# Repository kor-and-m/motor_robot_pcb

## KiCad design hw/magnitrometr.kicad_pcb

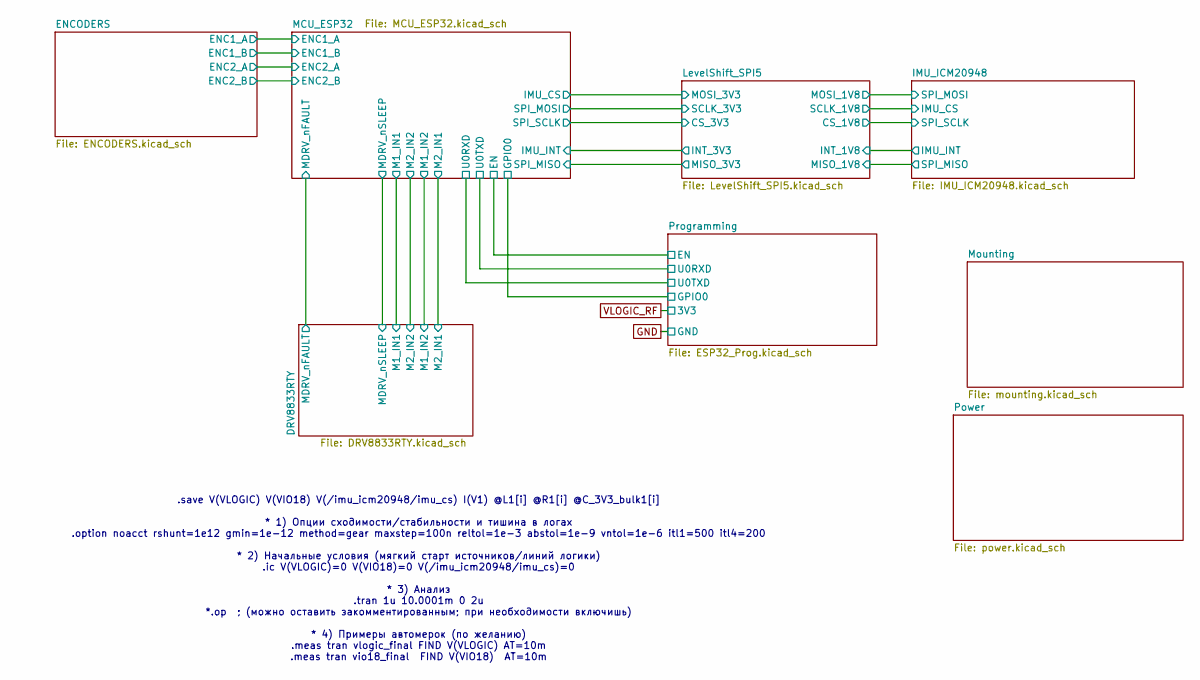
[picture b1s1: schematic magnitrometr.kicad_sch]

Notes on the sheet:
.save V(VLOGIC) V(VIO18) V(/imu_icm20948/imu_cs) I(V1) @L1[i] @R1[i] @C_3V3_bulk1[i] * 1) Опции сходимости/стабильности и тишина в логах .option noacct rshunt=1e12 gmin=1e-12 method=gear maxstep=100n reltol=1e-3 abstol=1e-9 vntol=1e-6 itl1=500 itl4=200 * 2) Начальные условия (мягкий старт источнико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

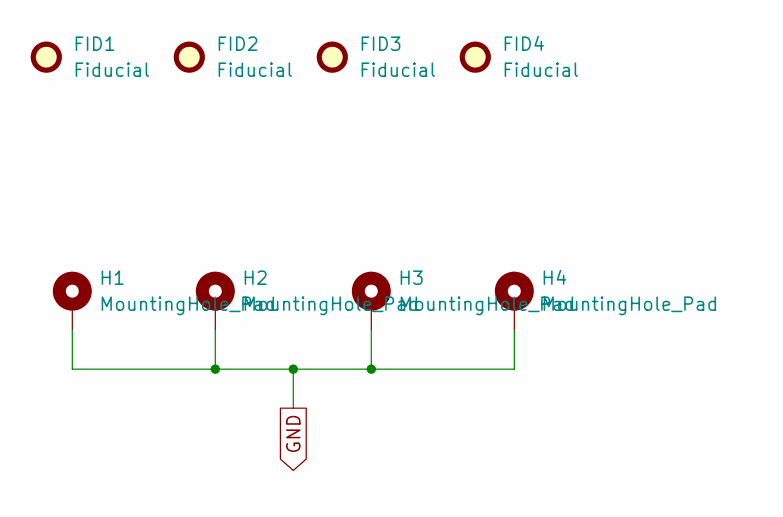
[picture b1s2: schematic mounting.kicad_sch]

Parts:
FID1, FID2, FID3, FID4: Fiducial; Fiducial_1.5mm_Mask3mm
H1, H2, H3, H4: MountingHole_Pad; MountingHole_3.2mm_M3_Pad

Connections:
GND: H1.1, H2.1, H3.1, H4.1; also elsewhere on the board

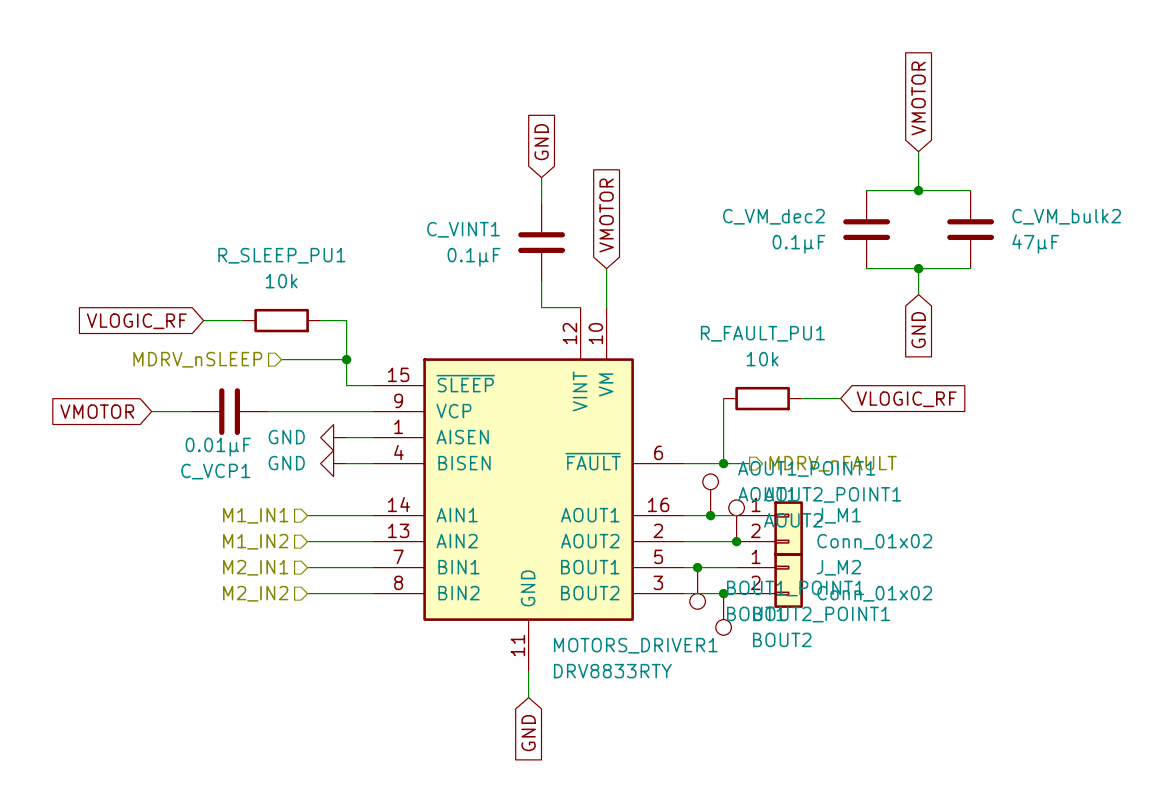
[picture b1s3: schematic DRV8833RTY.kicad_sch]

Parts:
AOUT1_POINT1: AOUT1; TestPoint_Pad_1.0x1.0mm
AOUT2_POINT1: AOUT2; TestPoint_Pad_1.0x1.0mm
BOUT1_POINT1: BOUT1; TestPoint_Pad_1.0x1.0mm
BOUT2_POINT1: BOUT2; TestPoint_Pad_1.0x1.0mm
C_VCP1: 0.01µF; C_0603_1608Metric
C_VINT1: 0.1µF; C_0603_1608Metric
C_VM_bulk2: 47µF; CP_Elec_5x5.8
C_VM_dec2: 0.1µF; C_0603_1608Metric
J_M1, J_M2: Conn_01x02; JST_VH_B2P-VH-B_1x02_P3.96mm_Vertical
MOTORS_DRIVER1: DRV8833RTY; Texas_RTY_WQFN-16-1EP_4x4mm_P0.65mm_EP2.1x2.1mm_ThermalVias
R_FAULT_PU1: 10k; R_0612_1632Metric
R_SLEEP_PU1: 10k; R_0612_1632Metric

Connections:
/DRV8833RTY/M1_IN1: MOTORS_DRIVER1.14 (AIN1); also elsewhere on the board
/DRV8833RTY/M1_IN2: MOTORS_DRIVER1.13 (AIN2); also elsewhere on the board
/DRV8833RTY/M2_IN1: MOTORS_DRIVER1.7 (BIN1); also elsewhere on the board
/DRV8833RTY/M2_IN2: MOTORS_DRIVER1.8 (BIN2); also elsewhere on the board
/DRV8833RTY/MDRV_nFAULT: MOTORS_DRIVER1.6 (~FAULT), R_FAULT_PU1.1; also elsewhere on the board
/DRV8833RTY/MDRV_nSLEEP: MOTORS_DRIVER1.15 (~SLEEP), R_SLEEP_PU1.2; also elsewhere on the board
GND: C_VINT1.1, C_VM_bulk2.2, C_VM_dec2.2, MOTORS_DRIVER1.1 (AISEN), MOTORS_DRIVER1.4 (BISEN), MOTORS_DRIVER1.11 (GND), MOTORS_DRIVER1.17 (GND); also elsewhere on the board
unnamed: AOUT1_POINT1.1, J_M1.1, MOTORS_DRIVER1.16 (AOUT1)
unnamed: AOUT2_POINT1.1, J_M1.2, MOTORS_DRIVER1.2 (AOUT2)
unnamed: BOUT1_POINT1.1, J_M2.1, MOTORS_DRIVER1.5 (BOUT1)
unnamed: BOUT2_POINT1.1, J_M2.2, MOTORS_DRIVER1.3 (BOUT2)
unnamed: C_VCP1.1, MOTORS_DRIVER1.9 (VCP)
unnamed: C_VINT1.2, MOTORS_DRIVER1.12 (VINT)
VLOGIC_RF: R_FAULT_PU1.2, R_SLEEP_PU1.1; also elsewhere on the board
VMOTOR: C_VCP1.2, C_VM_bulk2.1, C_VM_dec2.1, MOTORS_DRIVER1.10 (VM); also elsewhere on the board

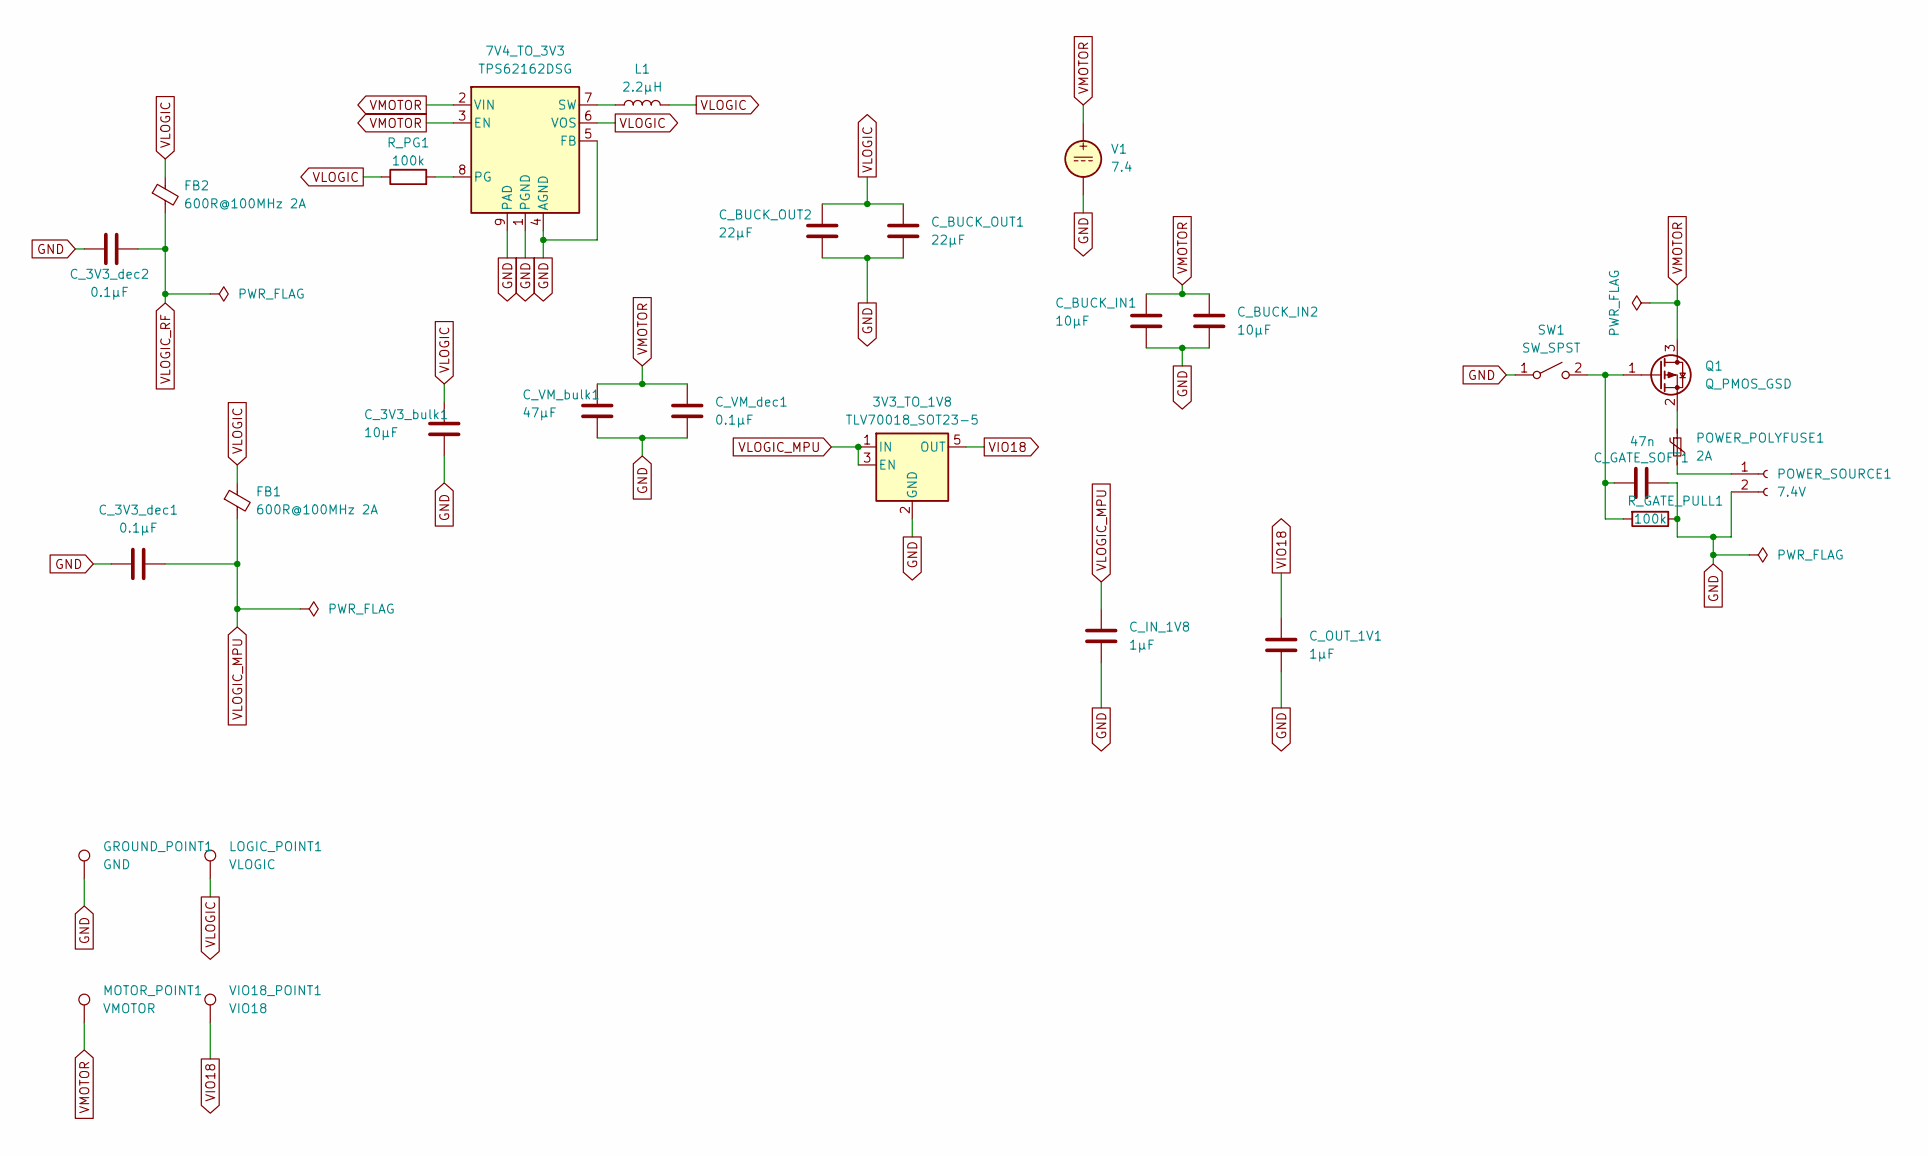
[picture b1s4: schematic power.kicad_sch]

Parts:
3V3_TO_1V8: TLV70018_SOT23-5; SOT-23-5
7V4_TO_3V3: TPS62162DSG; WSON-8-1EP_2x2mm_P0.5mm_EP0.9x1.6mm_ThermalVias
C_3V3_bulk1: 10µF; C_0805_2012Metric
C_3V3_dec1, C_3V3_dec2: 0.1µF; C_0603_1608Metric
C_BUCK_IN1, C_BUCK_IN2: 10µF; C_0805_2012Metric
C_BUCK_OUT1, C_BUCK_OUT2: 22µF; C_0805_2012Metric
C_GATE_SOFT1: 47n; C_0805_2012Metric
C_IN_1V8: 1µF; C_0603_1608Metric
C_OUT_1V1: 1µF; C_0603_1608Metric
C_VM_bulk1: 47µF; CP_Elec_5x5.8
C_VM_dec1: 0.1µF; C_0603_1608Metric
FB1, FB2: 600R@100MHz 2A; L_0805_2012Metric
GROUND_POINT1: GND; TestPoint_Pad_1.0x1.0mm
L1: 2.2µH; L_1008_2520Metric
LOGIC_POINT1: VLOGIC; TestPoint_Pad_1.0x1.0mm
MOTOR_POINT1: VMOTOR; TestPoint_Pad_1.0x1.0mm
POWER_POLYFUSE1: 2A; Fuse_Bourns_MF-RHT200
POWER_SOURCE1: 7.4V; TerminalBlock_bornier-2_P5.08mm
Q1: Q_PMOS_GSD; SOT-23
R_GATE_PULL1: 100k; R_0612_1632Metric
R_PG1: 100k; R_0603_1608Metric
SW1: SW_SPST; SW_SPDT_PCM12
V1: 7.4
VIO18_POINT1: VIO18; TestPoint_Pad_1.0x1.0mm

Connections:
GND: 3V3_TO_1V8.2 (GND), 7V4_TO_3V3.1 (PGND), 7V4_TO_3V3.4 (AGND), 7V4_TO_3V3.5 (FB), 7V4_TO_3V3.9 (PAD), C_3V3_bulk1.2, C_3V3_dec1.2, C_3V3_dec2.2, C_BUCK_IN1.2, C_BUCK_IN2.2, C_BUCK_OUT1.2, C_BUCK_OUT2.2, C_GATE_SOFT1.1, C_IN_1V8.2, C_OUT_1V1.2, C_VM_bulk1.2, C_VM_dec1.2, GROUND_POINT1.1, POWER_SOURCE1.2, R_GATE_PULL1.1, SW1.1 (A), V1.2; also elsewhere on the board
unnamed: 7V4_TO_3V3.8 (PG), R_PG1.2
unnamed: 7V4_TO_3V3.7 (SW), L1.1
unnamed: POWER_POLYFUSE1.2, POWER_SOURCE1.1
unnamed: C_GATE_SOFT1.2, Q1.1 (G), R_GATE_PULL1.2, SW1.2 (B)
unnamed: POWER_POLYFUSE1.1, Q1.2 (S)
VIO18: 3V3_TO_1V8.5 (OUT), C_OUT_1V1.1, VIO18_POINT1.1; also elsewhere on the board
VLOGIC: 7V4_TO_3V3.6 (VOS), C_3V3_bulk1.1, C_BUCK_OUT1.1, C_BUCK_OUT2.1, FB1.1, FB2.1, L1.2, LOGIC_POINT1.1, R_PG1.1
VLOGIC_MPU: 3V3_TO_1V8.1 (IN), 3V3_TO_1V8.3 (EN), C_3V3_dec1.1, C_IN_1V8.1, FB1.2; also elsewhere on the board
VLOGIC_RF: C_3V3_dec2.1, FB2.2; also elsewhere on the board
VMOTOR: 7V4_TO_3V3.2 (VIN), 7V4_TO_3V3.3 (EN), C_BUCK_IN1.1, C_BUCK_IN2.1, C_VM_bulk1.1, C_VM_dec1.1, MOTOR_POINT1.1, Q1.3 (D), V1.1; also elsewhere on the board

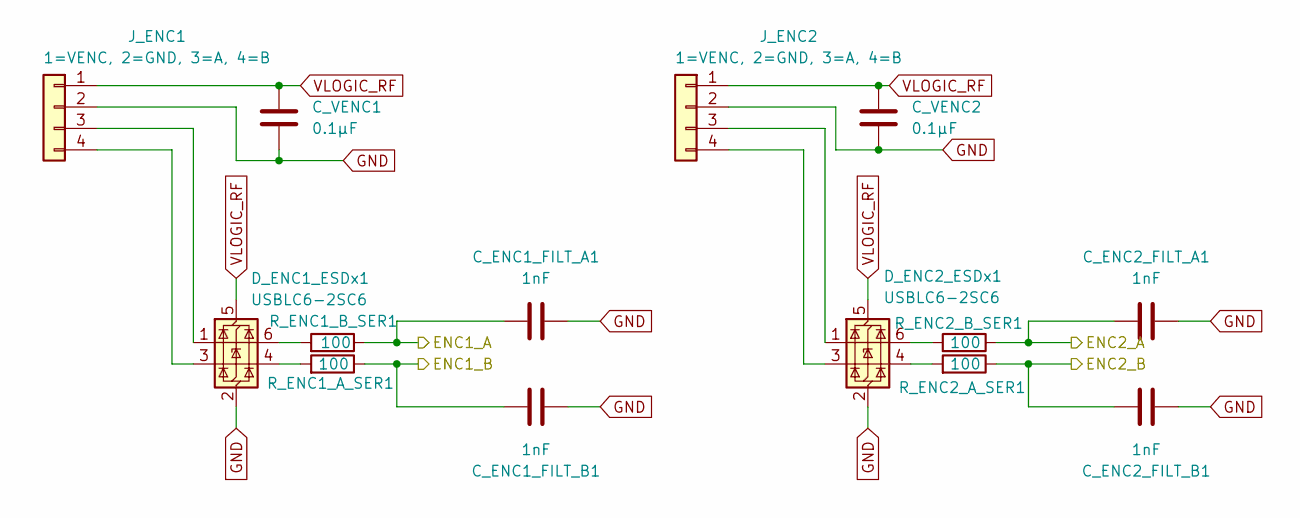
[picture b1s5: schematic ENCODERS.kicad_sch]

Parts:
C_ENC1_FILT_A1, C_ENC1_FILT_B1, C_ENC2_FILT_A1, C_ENC2_FILT_B1: 1nF; C_0603_1608Metric
C_VENC1, C_VENC2: 0.1µF; C_0603_1608Metric
D_ENC1_ESDx1, D_ENC2_ESDx1: USBLC6-2SC6; SOT-23-6
J_ENC1, J_ENC2: 1=VENC, 2=GND, 3=A, 4=B; JST_PH_B4B-PH-K_1x04_P2.00mm_Vertical
R_ENC1_A_SER1, R_ENC1_B_SER1, R_ENC2_A_SER1, R_ENC2_B_SER1: 100; R_0612_1632Metric

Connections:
/ENCODERS/ENC1_A: C_ENC1_FILT_A1.1, R_ENC1_B_SER1.1; also elsewhere on the board
/ENCODERS/ENC1_B: C_ENC1_FILT_B1.1, R_ENC1_A_SER1.1; also elsewhere on the board
/ENCODERS/ENC2_A: C_ENC2_FILT_A1.1, R_ENC2_B_SER1.1; also elsewhere on the board
/ENCODERS/ENC2_B: C_ENC2_FILT_B1.1, R_ENC2_A_SER1.1; also elsewhere on the board
GND: C_ENC1_FILT_A1.2, C_ENC1_FILT_B1.2, C_ENC2_FILT_A1.2, C_ENC2_FILT_B1.2, C_VENC1.2, C_VENC2.2, D_ENC1_ESDx1.2 (GND), D_ENC2_ESDx1.2 (GND), J_ENC1.2, J_ENC2.2; also elsewhere on the board
unnamed: D_ENC1_ESDx1.6 (I/O1), R_ENC1_B_SER1.2
unnamed: D_ENC1_ESDx1.4 (I/O2), R_ENC1_A_SER1.2
unnamed: D_ENC2_ESDx1.6 (I/O1), R_ENC2_B_SER1.2
unnamed: D_ENC2_ESDx1.4 (I/O2), R_ENC2_A_SER1.2
unnamed: D_ENC1_ESDx1.1 (I/O1), J_ENC1.3
unnamed: D_ENC1_ESDx1.3 (I/O2), J_ENC1.4
unnamed: D_ENC2_ESDx1.1 (I/O1), J_ENC2.3
unnamed: D_ENC2_ESDx1.3 (I/O2), J_ENC2.4
VLOGIC_RF: C_VENC1.1, C_VENC2.1, D_ENC1_ESDx1.5 (VBUS), D_ENC2_ESDx1.5 (VBUS), J_ENC1.1, J_ENC2.1; also elsewhere on the board

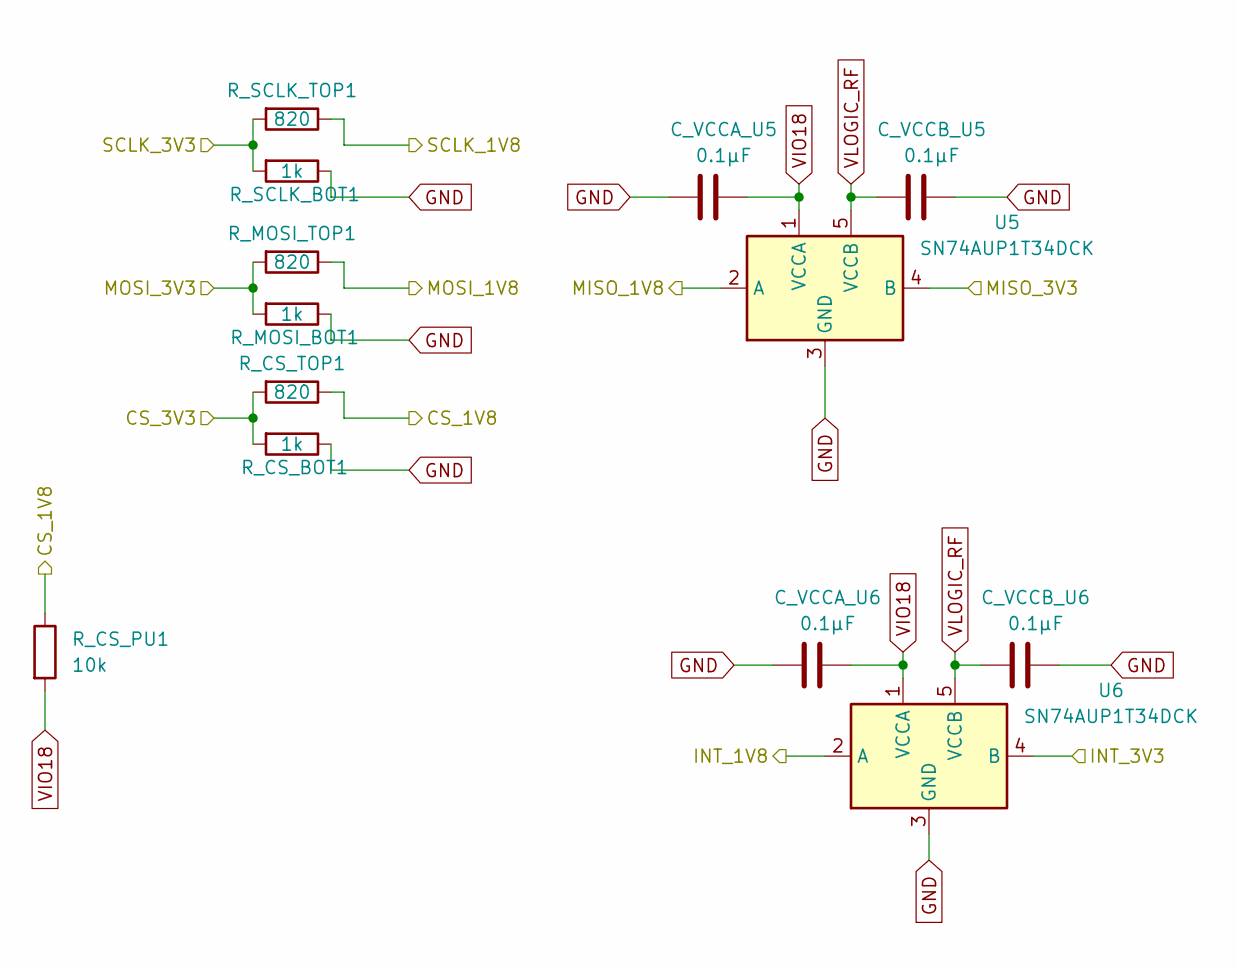
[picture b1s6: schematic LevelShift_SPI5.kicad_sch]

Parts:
C_VCCA_U5, C_VCCA_U6: 0.1µF; C_0603_1608Metric
C_VCCB_U5, C_VCCB_U6: 0.1µF; C_0603_1608Metric
R_CS_BOT1: 1k; R_0603_1608Metric
R_CS_PU1: 10k; R_0603_1608Metric
R_CS_TOP1: 820; R_0603_1608Metric
R_MOSI_BOT1: 1k; R_0603_1608Metric
R_MOSI_TOP1: 820; R_0603_1608Metric
R_SCLK_BOT1: 1k; R_0603_1608Metric
R_SCLK_TOP1: 820; R_0603_1608Metric
U5, U6: SN74AUP1T34DCK; SOT-353_SC-70-5

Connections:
/IMU_ICM20948/IMU_CS: R_SCLK_TOP1.1; also elsewhere on the board
/IMU_ICM20948/IMU_INT: U6.2 (A); also elsewhere on the board
/IMU_ICM20948/SPI_MISO: U5.2 (A); also elsewhere on the board
/IMU_ICM20948/SPI_MOSI: R_MOSI_TOP1.1; also elsewhere on the board
/IMU_ICM20948/SPI_SCLK: R_CS_PU1.1, R_CS_TOP1.1; also elsewhere on the board
/LevelShift_SPI5/CS_3V3: R_CS_BOT1.2, R_CS_TOP1.2; also elsewhere on the board
/LevelShift_SPI5/INT_3V3: U6.4 (B); also elsewhere on the board
/LevelShift_SPI5/MISO_3V3: U5.4 (B); also elsewhere on the board
/LevelShift_SPI5/MOSI_3V3: R_MOSI_BOT1.2, R_MOSI_TOP1.2; also elsewhere on the board
/LevelShift_SPI5/SCLK_3V3: R_SCLK_BOT1.2, R_SCLK_TOP1.2; also elsewhere on the board
GND: C_VCCA_U5.2, C_VCCA_U6.2, C_VCCB_U5.1, C_VCCB_U6.1, R_CS_BOT1.1, R_MOSI_BOT1.1, R_SCLK_BOT1.1, U5.3 (GND), U6.3 (GND); also elsewhere on the board
VIO18: C_VCCA_U5.1, C_VCCA_U6.1, R_CS_PU1.2, U5.1 (VCCA), U6.1 (VCCA); also elsewhere on the board
VLOGIC_RF: C_VCCB_U5.2, C_VCCB_U6.2, U5.5 (VCCB), U6.5 (VCCB); also elsewhere on the board

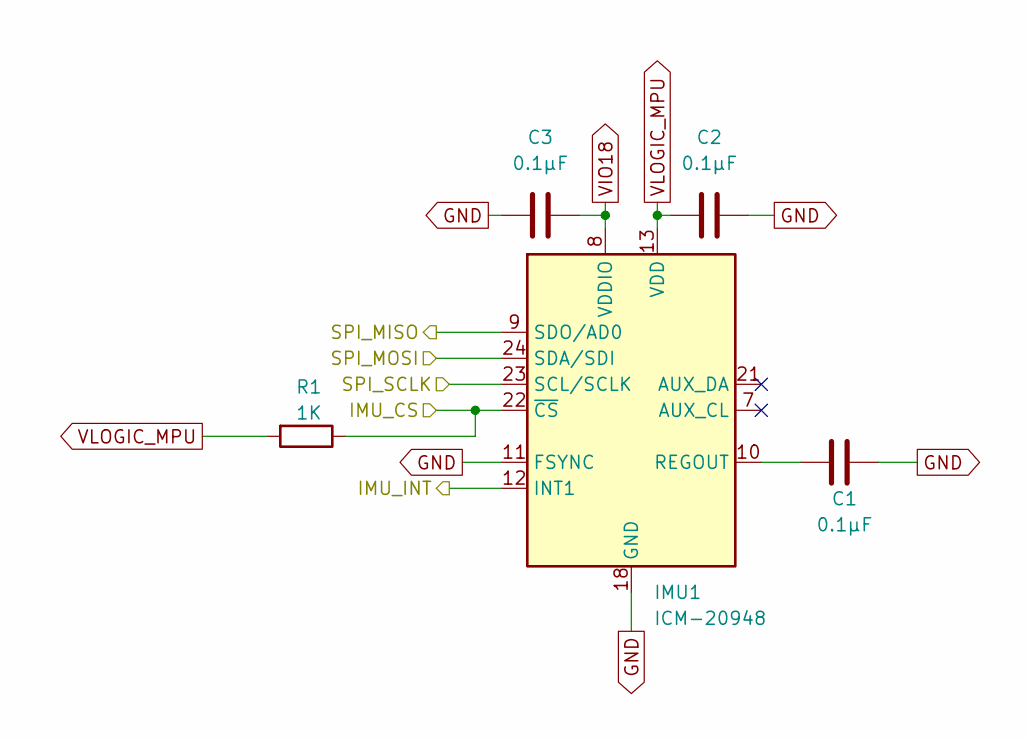
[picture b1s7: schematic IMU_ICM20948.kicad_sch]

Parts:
C1, C2, C3: 0.1µF; C_0603_1608Metric
IMU1: ICM-20948; InvenSense_QFN-24_3x3mm_P0.4mm
R1: 1K; R_0603_1608Metric

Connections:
/IMU_ICM20948/IMU_CS: IMU1.22 (~CS), R1.1; also elsewhere on the board
/IMU_ICM20948/IMU_INT: IMU1.12 (INT1); also elsewhere on the board
/IMU_ICM20948/SPI_MISO: IMU1.9 (SDO/AD0); also elsewhere on the board
/IMU_ICM20948/SPI_MOSI: IMU1.24 (SDA/SDI); also elsewhere on the board
/IMU_ICM20948/SPI_SCLK: IMU1.23 (SCL/SCLK); also elsewhere on the board
GND: C1.1, C2.1, C3.2, IMU1.11 (FSYNC), IMU1.18 (GND), IMU1.20 (GND); also elsewhere on the board
unnamed: C1.2, IMU1.10 (REGOUT)
VIO18: C3.1, IMU1.8 (VDDIO); also elsewhere on the board
VLOGIC_MPU: C2.2, IMU1.13 (VDD), R1.2; also elsewhere on the board

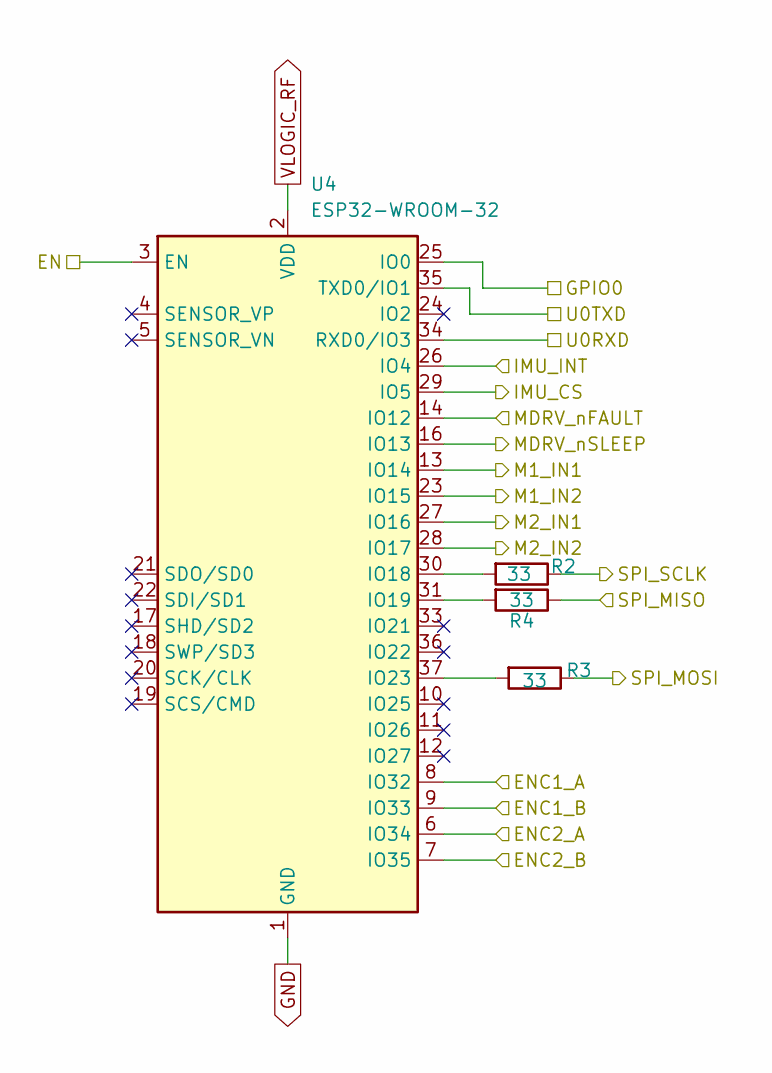
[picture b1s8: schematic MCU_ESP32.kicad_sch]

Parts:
R2, R3, R4: 33; R_0603_1608Metric
U4: ESP32-WROOM-32

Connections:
/DRV8833RTY/M1_IN1: U4.13 (IO14); also elsewhere on the board
/DRV8833RTY/M1_IN2: U4.23 (IO15); also elsewhere on the board
/DRV8833RTY/M2_IN1: U4.27 (IO16); also elsewhere on the board
/DRV8833RTY/M2_IN2: U4.28 (IO17); also elsewhere on the board
/DRV8833RTY/MDRV_nFAULT: U4.14 (IO12); also elsewhere on the board
/DRV8833RTY/MDRV_nSLEEP: U4.16 (IO13); also elsewhere on the board
/ENCODERS/ENC1_A: U4.8 (IO32); also elsewhere on the board
/ENCODERS/ENC1_B: U4.9 (IO33); also elsewhere on the board
/ENCODERS/ENC2_A: U4.6 (IO34); also elsewhere on the board
/ENCODERS/ENC2_B: U4.7 (IO35); also elsewhere on the board
/LevelShift_SPI5/CS_3V3: R2.1; also elsewhere on the board
/LevelShift_SPI5/INT_3V3: U4.26 (IO4); also elsewhere on the board
/LevelShift_SPI5/MISO_3V3: R4.1; also elsewhere on the board
/LevelShift_SPI5/MOSI_3V3: U4.29 (IO5); also elsewhere on the board
/LevelShift_SPI5/SCLK_3V3: R3.1; also elsewhere on the board
/MCU_ESP32/EN: U4.3 (EN); also elsewhere on the board
/MCU_ESP32/GPIO0: U4.25 (IO0); also elsewhere on the board
/MCU_ESP32/U0RXD: U4.34 (RXD0/IO3); also elsewhere on the board
/MCU_ESP32/U0TXD: U4.35 (TXD0/IO1); also elsewhere on the board
GND: U4.1 (GND), U4.15 (GND), U4.38 (GND), U4.39 (GND); also elsewhere on the board
unnamed: R2.2, U4.30 (IO18)
unnamed: R4.2, U4.31 (IO19)
unnamed: R3.2, U4.37 (IO23)
VLOGIC_RF: U4.2 (VDD); also elsewhere on the board

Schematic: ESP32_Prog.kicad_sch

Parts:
C_EN1: 100n; C_0603_1608Metric
J_PROG1: Conn_01x06; PinHeader_1x06_P2.54mm_Vertical
R_BOOT1: 10k; R_0603_1608Metric
R_EN1: 10k; R_0603_1608Metric
SW_BOOT1: BOOT; SW_SPST_TL3342
SW_RESET1: RESET; SW_SPST_TL3342

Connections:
/MCU_ESP32/EN: C_EN1.2, J_PROG1.4, R_EN1.1, SW_RESET1.1; also elsewhere on the board
/MCU_ESP32/GPIO0: J_PROG1.5, R_BOOT1.1, SW_BOOT1.1; also elsewhere on the board
/MCU_ESP32/U0RXD: J_PROG1.2; also elsewhere on the board
/MCU_ESP32/U0TXD: J_PROG1.3; also elsewhere on the board
GND: C_EN1.1, J_PROG1.1, SW_BOOT1.2, SW_RESET1.2; also elsewhere on the board
VLOGIC_RF: R_BOOT1.2, R_EN1.2; also elsewhere on the board

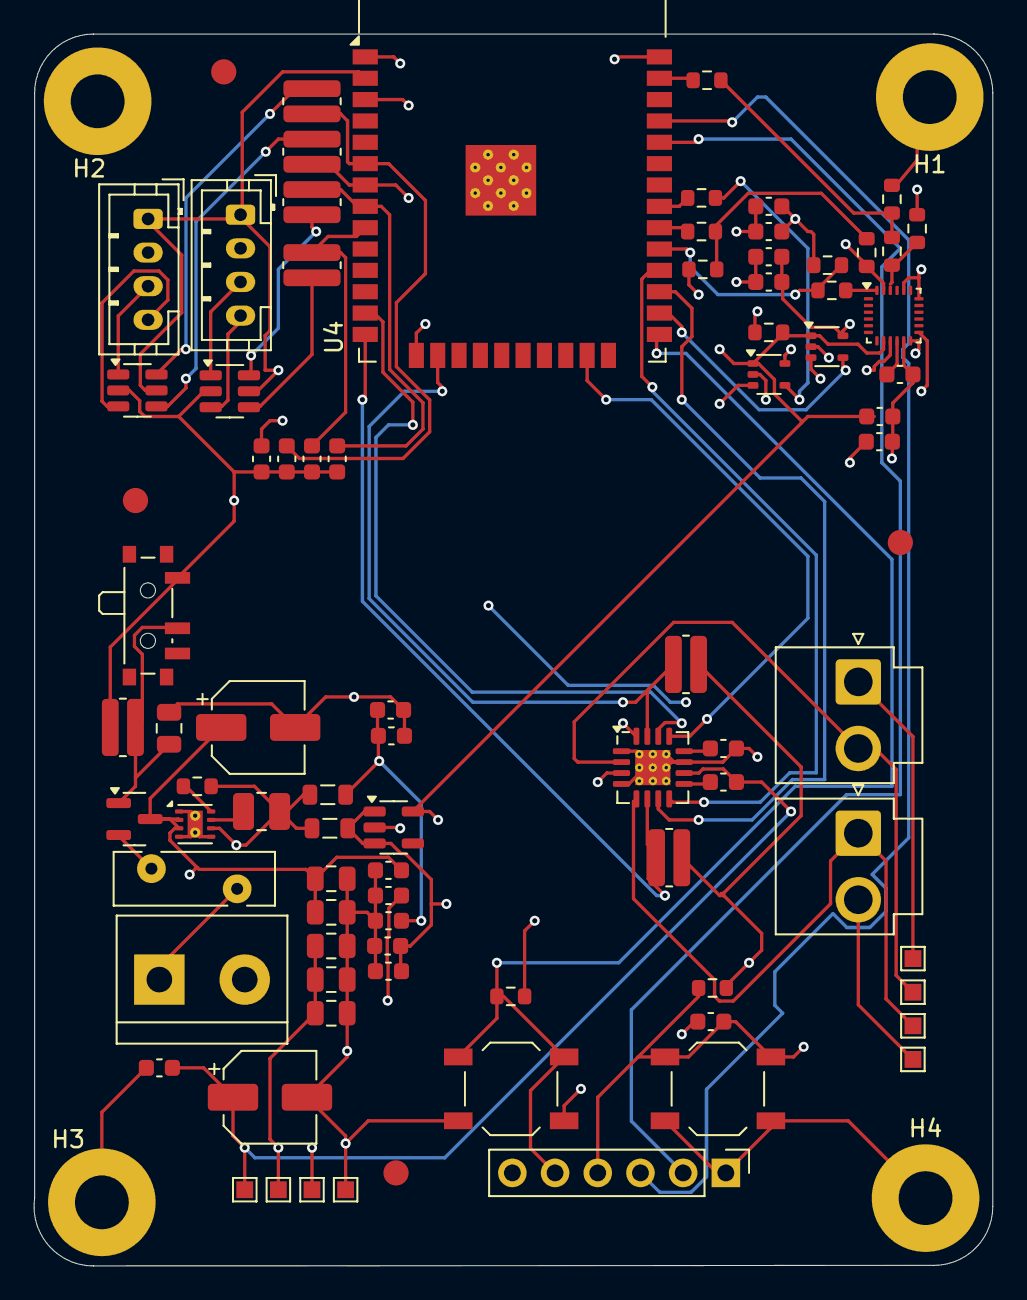
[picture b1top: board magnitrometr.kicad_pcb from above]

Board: 4 copper layers, 57.0 x 73.3 mm, 90 parts (0 on the bottom side), 53 nets.

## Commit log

2025-09-05 Initial
2025-09-05 Change project layout
2025-09-08 Add tests
